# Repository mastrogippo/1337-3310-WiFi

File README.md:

## 1337 3310 WiFi PCB and schematics

Writeup and pics [here](http://www.mastrogippo.it/2018/07/more-adventures-with-nokia-3310-teaser/) and [here](http://www.mastrogippo.it/2018/07/1337-3310-wifi-hardware-design/)

ESP32 firmware [here](https://github.com/IHCcamp/ihc-badge-esp32)

STM32 firmware [here](https://github.com/IHCcamp/ihc-badge-STM32)

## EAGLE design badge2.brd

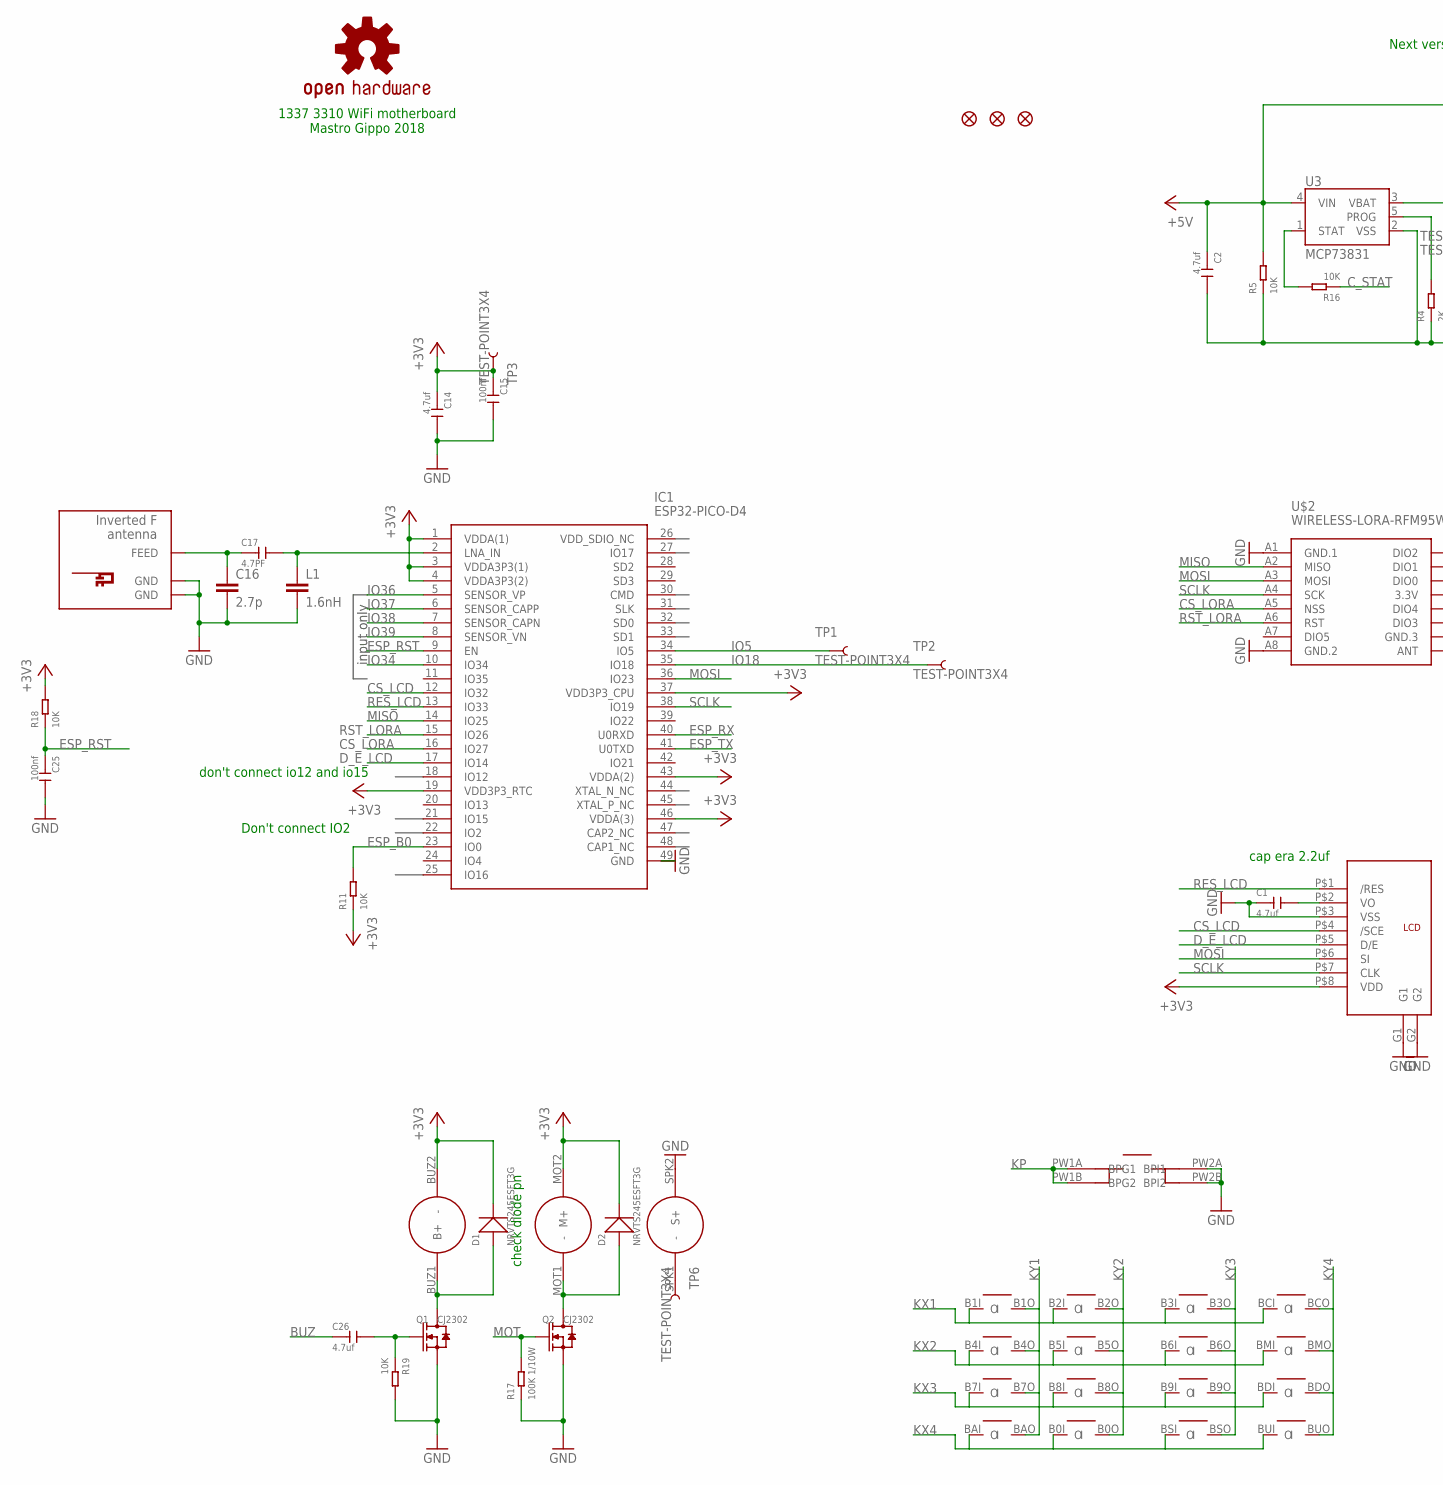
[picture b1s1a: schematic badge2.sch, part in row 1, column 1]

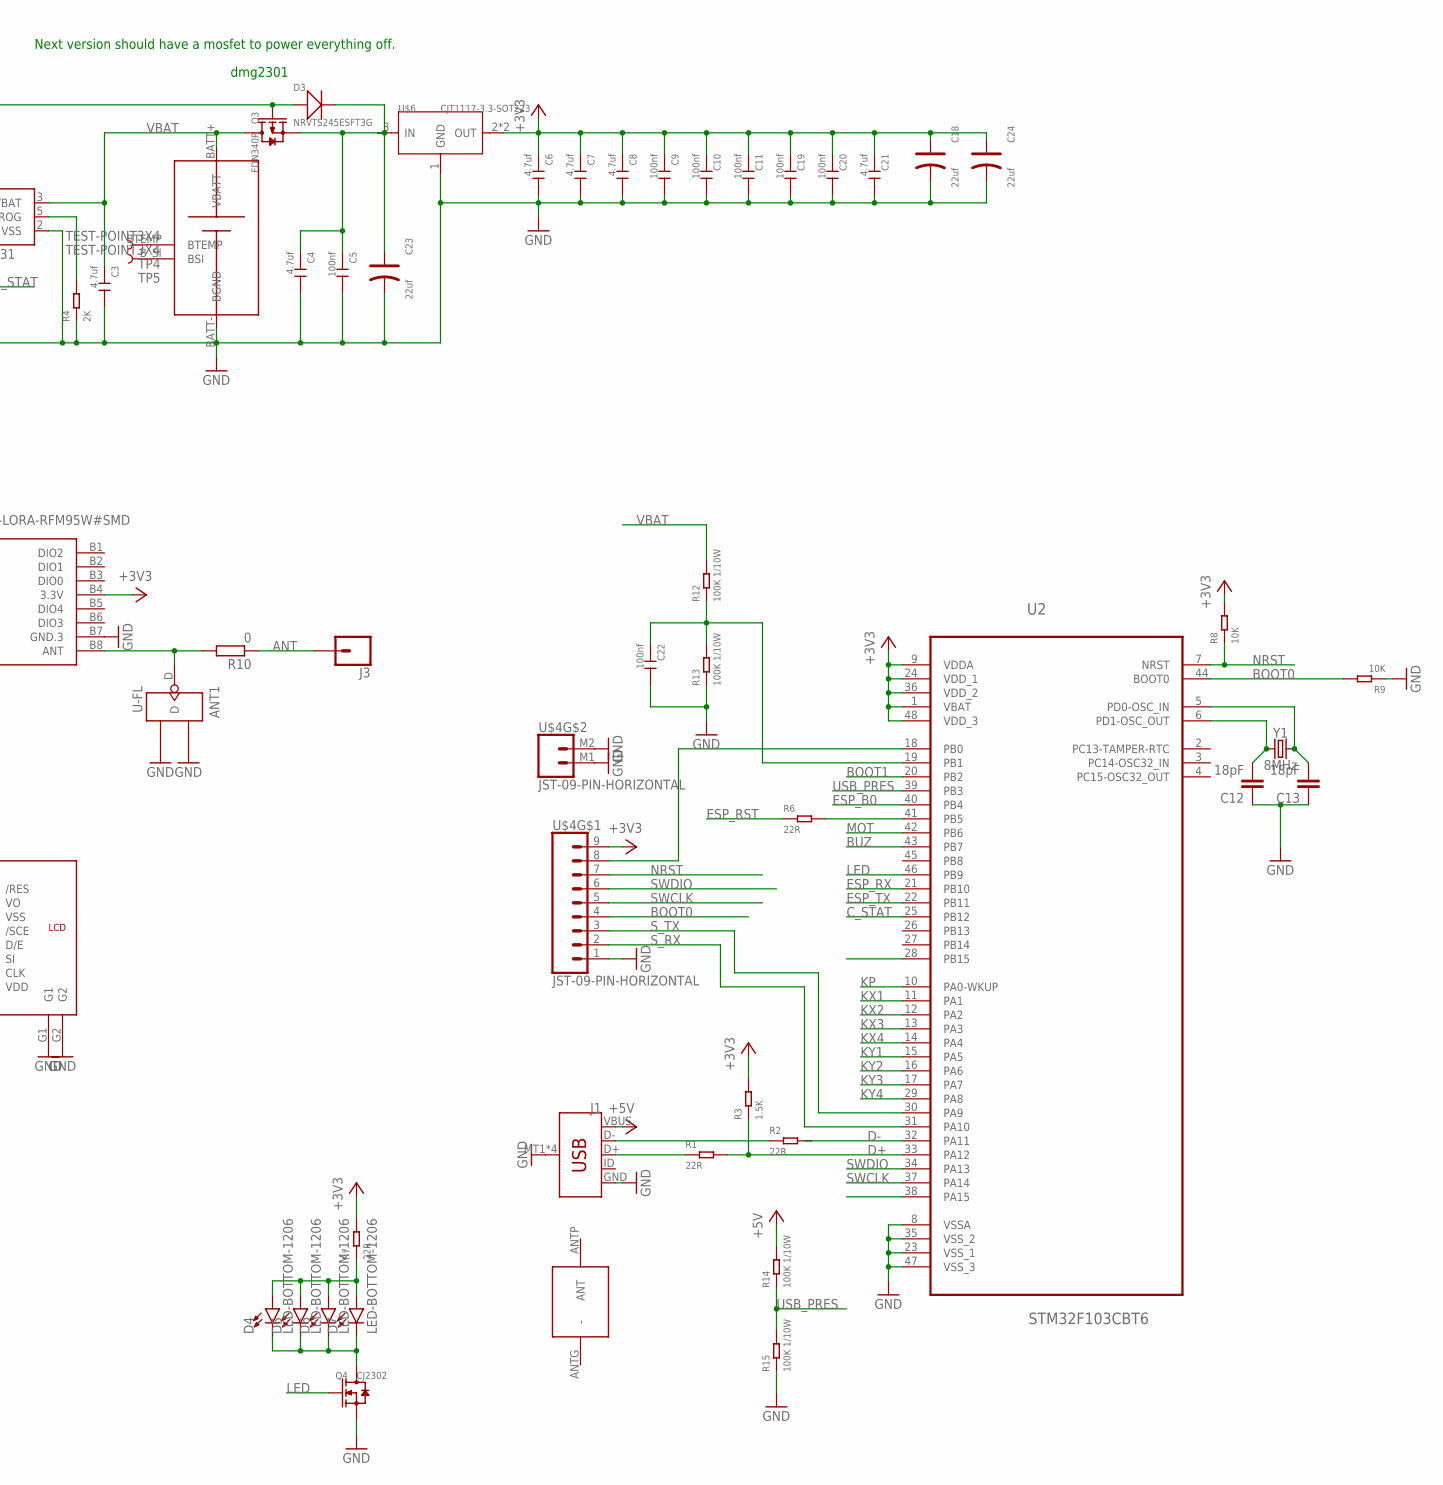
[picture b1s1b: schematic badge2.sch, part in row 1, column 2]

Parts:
ANT1: U-FL; U-FL3P-SMD-2.6X2.6X1.0MM
C1, C2, C3, C4, C6, C7, C8, C14, C21, C26: 4.7uf; C0603
C5, C9, C10, C11, C15, C19, C20, C22, C25: 100nf; C0603
C12, C13: 18pF; 0603
C16: 2.7p; C0603
C17: 4.7PF; C0603
C18, C23, C24: 22uf; AVX-B
D1, D2, D3: NRVTS245ESFT3G; SOD-123
D4, D5, D6, D7: LED-BOTTOM-1206; LED-1206
FID1, FID2, FID3: FIDUCIAL1.5X3; FIDUCIAL-1.5X3
IC1: ESP32-PICO-D4; ESP32-PICO-D4_1
J1: USB_MICRO-B_SMT; USB-MICROB
J3: CONN_01POGOPIN_HOLE_0.58; 1X01_POGOPIN_HOLE_0.58_DIA
L1: 1.6nH; C0603K
LOGO1: OSHW-LOGOM; OSHW-LOGO-M
Q1, Q2, Q4: CJ2302; SOT-23
Q3: FDN340P; SOT-23
R1, R2, R6, R7: 22R; R0603
R3: 1.5K; R0603
R4: 2K; R0603
R5, R8, R9, R11, R16, R18, R19: 10K; R0603
R10: 0; R0603
R12, R13, R14, R15, R17: 100K 1/10W; R0603
TP1, TP2, TP3, TP4, TP5, TP6: TEST-POINT3X4; PAD.03X.04
U2: STM32F103CBT6; QFP50P900X900X160-48N
U3: MCP73831; SOT23-5
U$1: 3310PANEL; 3310LCD
U$2: WIRELESS-LORA-RFM95W#SMD
U$3: INVERTED_F_ANTENNA+2; DN007+2
U$4: JST-09-PIN-HORIZONTAL; JST-09-SMD-HORI-1.0MM
U$6: CJT1117-3.3-SOT223; SOT-223
Y1: 8MHz; CRYSTAL-SMD-5X3.2-4PAD

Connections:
+3V3: C6.1, C7.1, C8.1, C9.1, C10.1, C11.1, C14.1, C15.1, C18.+, C19.1, C20.1, C21.1, C24.+, D1.-, D2.-, IC1.1 (VDDA(1)), IC1.3 (VDDA3P3(1)), IC1.4 (VDDA3P3(2)), IC1.19 (VDD3P3_RTC), IC1.37 (VDD3P3_CPU), IC1.43 (VDDA(2)), IC1.46 (VDDA(3)), R3.2, R7.2, R8.2, R11.1, R18.2, TP3.P$1, U2.1 (VBAT), U2.9 (VDDA), U2.24 (VDD_1), U2.36 (VDD_2), U2.48 (VDD_3), U$1.BUZ2 (-), U$1.MOT2 (M+), U$1.P$8 (VDD), U$2.B4 (3.3V), U$4.9, U$6.2 (OUT), U$6.TER (OUT)
+5V: C2.1, D3.+, J1.VBUS, Q3.1 (G), R5.2, R14.2, U3.4 (VIN)
ANT: J3.1, R10.1
BOOT0: R9.2, U2.44 (BOOT0), U$4.4
BOOT1: U2.20 (PB2)
BUZ: C26.1, U2.43 (PB7)
CS_LCD: IC1.12 (IO32), U$1.P$4 (/SCE)
CS_LORA: IC1.16 (IO27), U$2.A5 (NSS)
C_STAT: R16.1, U2.25 (PB12)
D+: R1.2, R3.1, U2.33 (PA12)
D-: R2.2, U2.32 (PA11)
D_E_LCD: IC1.17 (IO14), U$1.P$5 (D/E)
ESP_B0: IC1.23 (IO0), R11.2, U2.40 (PB4)
ESP_RST: C25.1, IC1.9 (EN), R6.1, R18.1
ESP_RX: IC1.40 (U0RXD), U2.21 (PB10)
ESP_TX: IC1.41 (U0TXD), U2.22 (PB11)
GND: ANT1.GND1, ANT1.GND2, C1.1, C2.2, C3.2, C4.2, C5.2, C6.2, C7.2, C8.2, C9.2, C10.2, C11.2, C12.1, C13.1, C14.2, C15.2, C16.2, C18.-, C19.2, C20.2, C21.2, C22.2, C23.-, C24.-, C25.2, IC1.49 (GND), J1.GND, J1.MT1 (SHIELD), J1.MT2 (SHIELD), J1.P$1 (SHIELD), J1.P$2 (SHIELD), L1.2, Q1.2 (S), Q2.2 (S), Q4.2 (S), R4.1, R5.1, R9.1, R13.1, R15.1, R17.1, R19.2, U2.8 (VSSA), U2.23 (VSS_1), U2.35 (VSS_2), U2.47 (VSS_3), U3.2 (VSS), U$1.BATT- (BGND), U$1.G1, U$1.G2, U$1.P$3 (VSS), U$1.PW2A (BPI1), U$1.PW2B (BPI2), U$1.SPK2 (S+), U$2.A1 (GND.1), U$2.A8 (GND.2), U$2.B7 (GND.3), U$3.GND, U$3.GND@1 (GND), U$4.1, U$4.M1 (1), U$4.M2 (2), U$6.1 (GND)
IO5: IC1.34 (IO5), TP1.P$1
IO18: IC1.35 (IO18), TP2.P$1
IO34: IC1.10 (IO34)
IO36: IC1.5 (SENSOR_VP)
IO37: IC1.6 (SENSOR_CAPP)
IO38: IC1.7 (SENSOR_CAPN)
IO39: IC1.8 (SENSOR_VN)
KP: U2.10 (PA0-WKUP), U$1.PW1A (BPG1), U$1.PW1B (BPG2)
KX1: U2.11 (PA1), U$1.B1I (I), U$1.B2I (I), U$1.B3I (I), U$1.BCI (I)
KX2: U2.12 (PA2), U$1.B4I (I), U$1.B5I (I), U$1.B6I (I), U$1.BMI (I)
KX3: U2.13 (PA3), U$1.B7I (I), U$1.B8I (I), U$1.B9I (I), U$1.BDI (I)
KX4: U2.14 (PA4), U$1.B0I (I), U$1.BAI (I), U$1.BSI (I), U$1.BUI (I)
KY1: U2.15 (PA5), U$1.B1O (O), U$1.B4O (O), U$1.B7O (O), U$1.BAO (O)
KY2: U2.16 (PA6), U$1.B0O (O), U$1.B2O (O), U$1.B5O (O), U$1.B8O (O)
KY3: U2.17 (PA7), U$1.B3O (O), U$1.B6O (O), U$1.B9O (O), U$1.BSO (O)
KY4: U2.29 (PA8), U$1.BCO (O), U$1.BDO (O), U$1.BMO (O), U$1.BUO (O)
LED: Q4.1 (G), U2.46 (PB9)
MISO: IC1.14 (IO25), U$2.A2 (MISO)
MOSI: IC1.36 (IO23), U$1.P$6 (SI), U$2.A3 (MOSI)
MOT: Q2.1 (G), R17.2, U2.42 (PB6)
unnamed: C1.2, U$1.P$2 (VO)
unnamed: C16.1, C17.1, U$3.FEED
unnamed: C17.2, IC1.2 (LNA_IN), L1.1
unnamed: ANT1.D, R10.2, U$2.B8 (ANT)
unnamed: J1.D+, R1.1
unnamed: J1.D-, R2.1
unnamed: R16.2, U3.1 (STAT)
unnamed: C26.2, Q1.1 (G), R19.1
unnamed: D1.+, Q1.3 (D), U$1.BUZ1 (B+)
unnamed: C13.2, U2.5 (PD0-OSC_IN), Y1.3 (2)
unnamed: TP4.P$1, U$1.BTEMP
unnamed: D2.+, Q2.3 (D), U$1.MOT1 (-)
unnamed: R4.2, U3.5 (PROG)
unnamed: C4.1, C5.1, C23.+, D3.-, Q3.2 (S), U$6.3 (IN)
unnamed: C12.2, U2.6 (PD1-OSC_OUT), Y1.1
unnamed: U2.18 (PB0), U$4.8
unnamed: TP6.P$1, U$1.SPK1 (-)
unnamed: R6.2, U2.41 (PB5)
unnamed: TP5.P$1, U$1.B_SI (BSI)
unnamed: D4.C, D5.C, D6.C, D7.C, Q4.3 (D)
unnamed: D4.A, D5.A, D6.A, D7.A, R7.1
unnamed: C22.1, R12.1, R13.2, U2.19 (PB1)
NRST: R8.1, U2.7 (NRST), U$4.7
RES_LCD: IC1.13 (IO33), U$1.P$1 (/RES)
RST_LORA: IC1.15 (IO26), U$2.A6 (RST)
SCLK: IC1.38 (IO19), U$1.P$7 (CLK), U$2.A4 (SCK)
SWCLK: U2.37 (PA14), U$4.5
SWDIO: U2.34 (PA13), U$4.6
S_RX: U2.31 (PA10), U$4.2
S_TX: U2.30 (PA9), U$4.3
USB_PRES: R14.1, R15.2, U2.39 (PB3)
VBAT: C3.1, Q3.3 (D), R12.2, U3.3 (VBAT), U$1.BATT+ (VBATT)

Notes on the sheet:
check diode pn
input only
Don't connect IO2
don't connect io12 and io15
dmg2301
cap era 2.2uf
Next version should have a mosfet to power everything off.
1337 3310 WiFi motherboard Mastro Gippo 2018

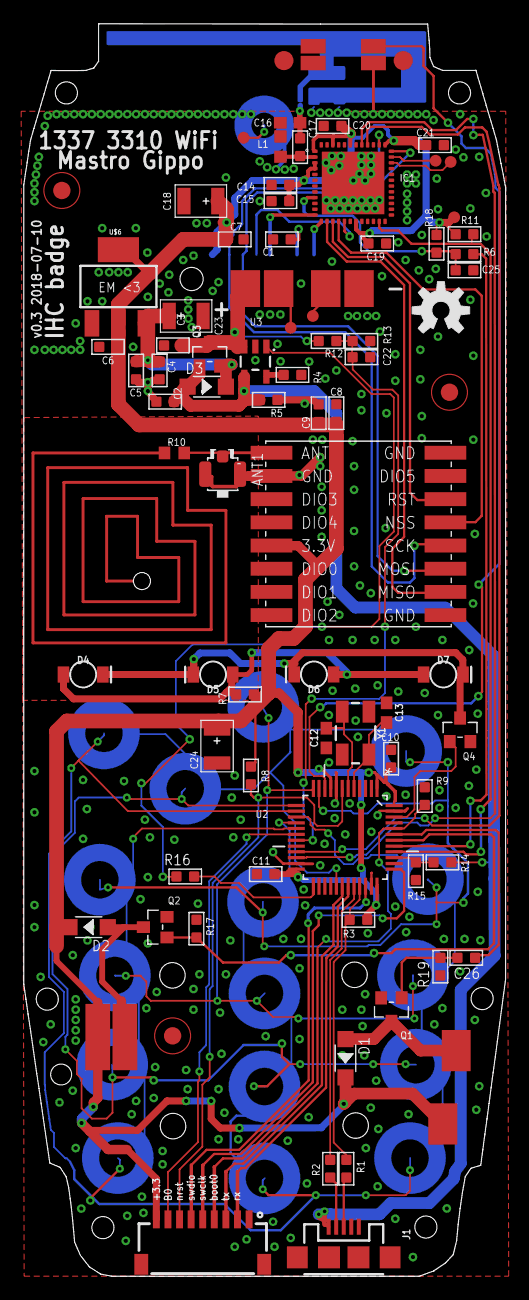
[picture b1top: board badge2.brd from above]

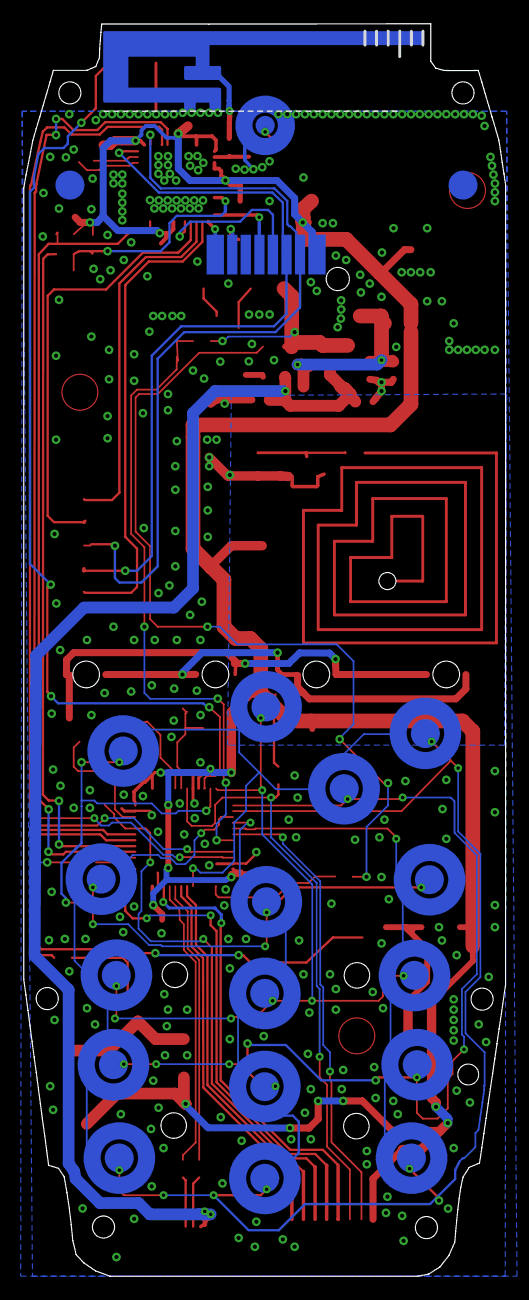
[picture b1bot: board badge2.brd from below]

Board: 2 copper layers, 41.6 x 108.0 mm, 79 parts (2 on the bottom side), 63 nets.

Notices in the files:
parts and their libraries:
SparkFun-Connectors: Licensing: Creative Commons ShareAlike 4.0 International - https://creativecommons.org/licenses/by-sa/4.0
diy-modules: Released under the Creative Commons Attribution 4.0 International License: http://creativecommons.org/licenses/by/4.0
